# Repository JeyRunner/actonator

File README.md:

## Actonator - 3D Printable Robot Actuator

3D printable robot actuator with belt-driven gearbox and custom FOC driver board for the used BLDC motor.
It uses the [CAN SOT Protocol](https://github.com/JeyRunner/can-sot-protocol) for the communication, which allows to not only send commands and receive state changes but also to set configuration parameters dynamically during runtime.

### Features

- Driver board
  - Input: 10 - 24V
  - Output: can drive up to two BLDC motors, each output up to 10A
  - CAN bus communication
  - Encoders connected via two I2C connections
      - Alternatively via two SPI inputs
    - 12 bit encoders
- Gearbox
  - Fully 3d printable
  - 2 stage timing belt based reduction
  - Simple screw-based belt tensioning mechanism
  - ~1:20 reduction
  - Easily back drivable

### Project Structure
- `motor_driver/firmware`: C++ firmware code for the stm32 microcontroller
- `motor_driver/can_client_lib`: Contains the can bus communication protocol definition and host applications to configure and interface with the motor driver.
    - `motorControllerCanProtocol.def.yaml`: Contains the protocol definition.
- `motor_driver/hardware`: Kicad files with schematics for the board and PCB.
- `motor_driver/hardware/output`: Schematics, board layout and manufacturing files.
- `gearbox`: 3D printing stl files for the gearbox.

### Driver Board Electronics
This board is a dual channel brushless motor driver.
The design of the board can be found in the `hardware` subfolder.
In `hardware/output` are all generated files for all versions.

For the full schematic, see [hardware/motorDriver/output/v0.0.1/schematic.pdf](motor_driver/hardware/output/v0.0.1/schematic.pdf).

### Gearbox

### Usage
First look at [motor_driver/can_client_lib/README.md](motor_driver/can_client_lib/README.md) to compile the communication lib and host control application.
Then compile and flash the microcontroller firmware, see [motor_driver/firmware/README.md](motor_driver/firmware/README.md).

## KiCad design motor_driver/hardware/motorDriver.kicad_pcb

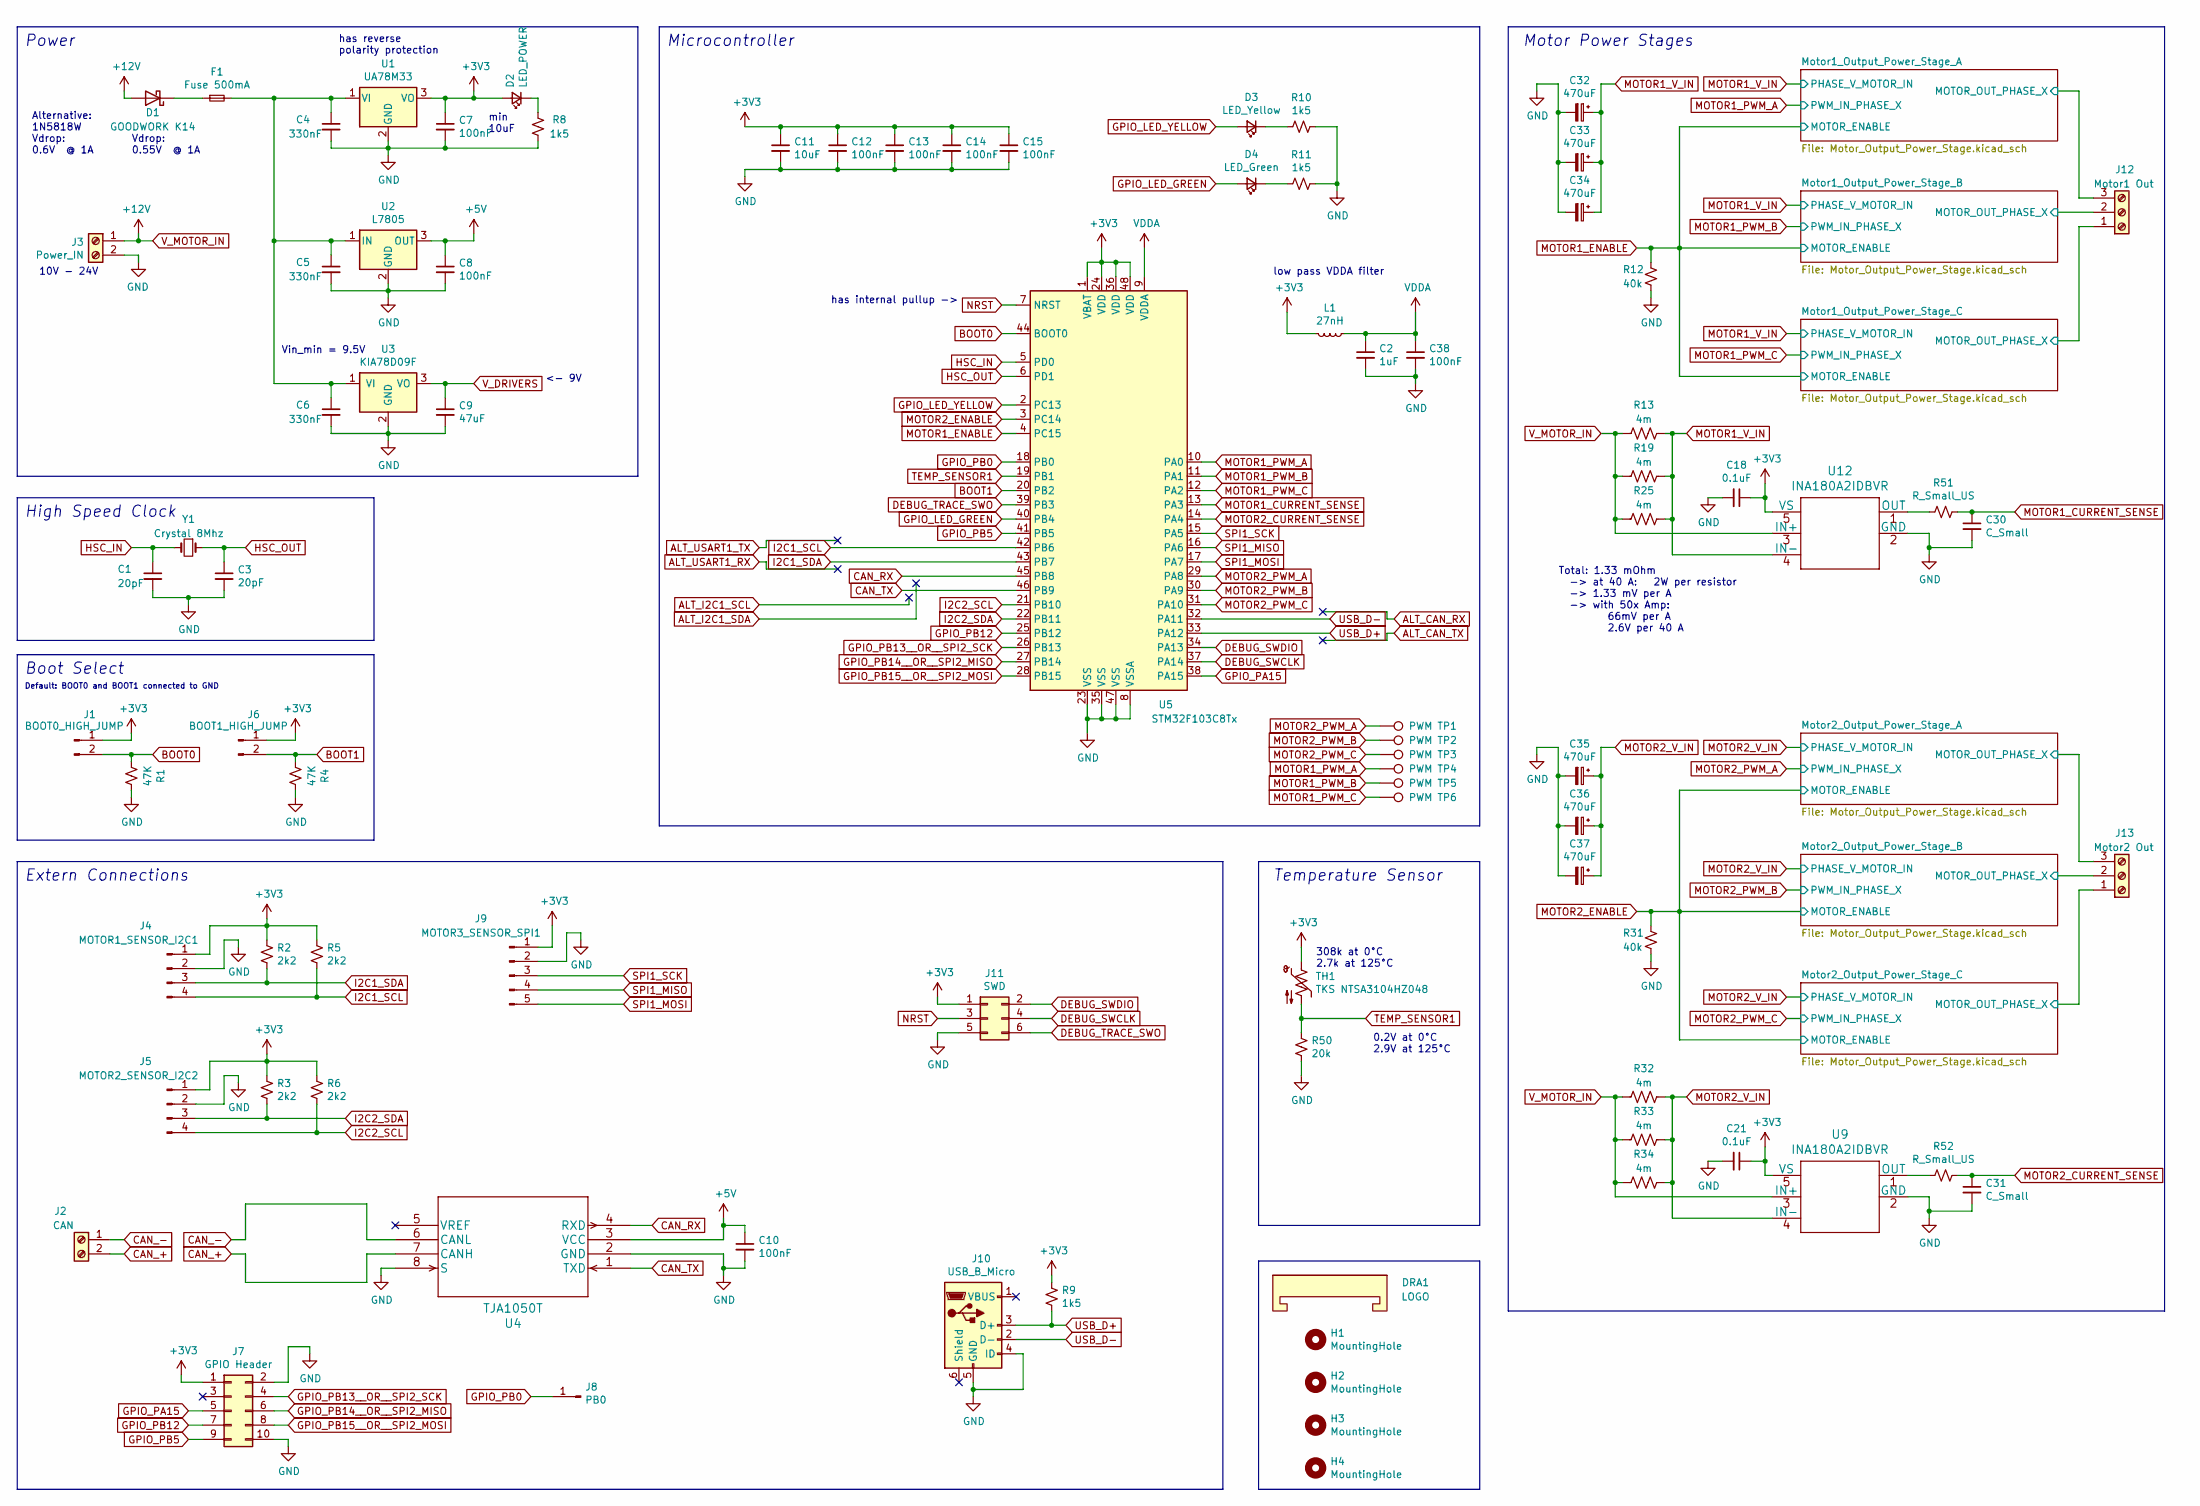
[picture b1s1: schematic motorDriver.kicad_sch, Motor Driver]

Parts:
C1, C3: 20pF; C_0805_2012Metric_Pad1.15x1.40mm_HandSolder
C2: 1uF; C_0805_2012Metric_Pad1.15x1.40mm_HandSolder
C4, C5, C6: 330nF; C_0805_2012Metric_Pad1.15x1.40mm_HandSolder
C7, C8, C10, C12, C13, C14, C15, C38: 100nF; C_0805_2012Metric_Pad1.15x1.40mm_HandSolder
C9: 47uF; C_1210_3225Metric_Pad1.42x2.65mm_HandSolder
C11: 10uF; C_0805_2012Metric_Pad1.15x1.40mm_HandSolder
C18, C21: 0.1uF; C_0805_2012Metric_Pad1.15x1.40mm_HandSolder
C30, C31: C_Small; C_0805_2012Metric_Pad1.15x1.40mm_HandSolder
C32, C33, C34, C35, C36, C37: 470uF; CP_Elec_10x10.5
D1: GOODWORK K14; D_SOD-123F
D2: LED_POWER; LED_0805_2012Metric_Pad1.15x1.40mm_HandSolder
D3: LED_Yellow; LED_0805_2012Metric_Pad1.15x1.40mm_HandSolder
D4: LED_Green; LED_0805_2012Metric_Pad1.15x1.40mm_HandSolder
DRA1: LOGO; logo
F1: Fuse 500mA; Fuse_1206_3216Metric_Pad1.42x1.75mm_HandSolder
H1, H2, H3, H4: MountingHole; MountingHole_3.2mm_M3_DIN965_Pad
J1: BOOT0_HIGH_JUMP; PinHeader_1x02_P1.27mm_Vertical__smallerOutline
J2: CAN; TerminalBlock_RND_205-00045_1x02_P5.00mm_Horizontal
J3: Power_IN; TerminalBlock_RND_205-00045_1x02_P5.00mm_Horizontal___with_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
J4: MOTOR1_SENSOR_I2C1; PinHeader_1x04_P2.54mm_Vertical
J5: MOTOR2_SENSOR_I2C2; PinHeader_1x04_P2.54mm_Vertical
J6: BOOT1_HIGH_JUMP; PinHeader_1x02_P1.27mm_Vertical__smallerOutline
J7: GPIO Header; PinSocket_2x05_P2.54mm_Vertical
J8: PB0; TestPoint_Pad_D1.5mm
J9: MOTOR3_SENSOR_SPI1; PinHeader_1x05_P2.54mm_Vertical
J10: USB_B_Micro; XKB_U254-051T-4BH83-F1S
J11: SWD; PinHeader_2x03_P2.54mm_Vertical
J12: Motor1 Out; TerminalBlock_RND_205-00046_1x03_P5.00mm_Horizontal__extend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
J13: Motor2 Out; TerminalBlock_RND_205-00046_1x03_P5.00mm_Horizontal__extend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
L1: 27nH; L_0603_1608Metric_Pad1.05x0.95mm_HandSolder
R1, R4: 47K; R_1206_3216Metric_Pad1.42x1.75mm_HandSolder
R2, R3, R5, R6: 2k2; R_1206_3216Metric_Pad1.42x1.75mm_HandSolder
R8, R9, R10, R11: 1k5; R_1206_3216Metric_Pad1.42x1.75mm_HandSolder
R12, R31: 40k; R_1206_3216Metric_Pad1.42x1.75mm_HandSolder
R13, R19, R25, R32, R33, R34: 4m; R_2512_6332Metric_Pad1.52x3.35mm_HandSolder
R50: 20k; R_1206_3216Metric_Pad1.42x1.75mm_HandSolder
R51, R52: R_Small_US; R_1206_3216Metric_Pad1.42x1.75mm_HandSolder
TH1: TKS NTSA3104HZ048; TH_2PIN_1.27mm
TP1, TP2, TP3, TP4, TP5, TP6: PWM; TestPoint_Pad_D1.0mm
U1: UA78M33; SOT-223-3_TabPin2
U2: L7805; TO-252-2
U3: KIA78D09F; TO-252-2
U4: TJA1050T
U5: STM32F103C8Tx; LQFP-48_7x7mm_P0.5mm
U9, U12: INA180A2IDBVR; SOT-23-5_HandSoldering
Y1: Crystal 8Mhz; Crystal_HC50_Vertical

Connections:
+3V3: C7.1, C11.1, C12.1, C13.1, C14.1, C15.1, C18.1, C21.1, D2.2 (A), J1.1, J4.1, J5.1, J6.1, J7.1, J9.1, J11.1, L1.2, R2.1, R3.1, R5.1, R6.1, R9.1, TH1.1, U1.3 (VO), U5.1 (VBAT), U5.24 (VDD), U5.36 (VDD), U5.48 (VDD), U9.5 (VS), U12.5 (VS)
+5V: C8.1, C10.1, U2.3 (OUT), U4.3 (VCC)
/Motor1_Output_Power_Stage_A/MOTOR_OUT_PHASE_X: J12.3; also elsewhere on the board
/Motor1_Output_Power_Stage_B/MOTOR_OUT_PHASE_X: J12.2; also elsewhere on the board
/Motor1_Output_Power_Stage_C/MOTOR_OUT_PHASE_X: J12.1; also elsewhere on the board
/Motor2_Output_Power_Stage_A/MOTOR_OUT_PHASE_X: J13.3; also elsewhere on the board
/Motor2_Output_Power_Stage_B/MOTOR_OUT_PHASE_X: J13.2; also elsewhere on the board
/Motor2_Output_Power_Stage_C/MOTOR_OUT_PHASE_X: J13.1; also elsewhere on the board
BOOT0: J1.2, R1.2, U5.44 (BOOT0)
BOOT1: J6.2, R4.2, U5.20 (PB2)
CAN_+: J2.2, U4.7 (CANH)
CAN_-: J2.1, U4.6 (CANL)
CAN_RX: U4.4 (RXD), U5.45 (PB8)
CAN_TX: U4.1 (TXD), U5.46 (PB9)
DEBUG_SWCLK: J11.4, U5.37 (PA14)
DEBUG_SWDIO: J11.2, U5.34 (PA13)
DEBUG_TRACE_SWO: J11.6, U5.39 (PB3)
GND: C1.2, C2.2, C3.2, C4.2, C5.2, C6.2, C7.2, C8.2, C9.2, C10.2, C11.2, C12.2, C13.2, C14.2, C15.2, C18.2, C21.2, C30.2, C31.2, C32.2, C33.2, C34.2, C35.2, C36.2, C37.2, C38.2, J3.2, J4.2, J5.2, J7.2, J7.10, J9.2, J10.4 (ID), J10.5 (GND), J11.5, R1.1, R4.1, R8.1, R10.2, R11.2, R12.2, R31.2, R50.2, U1.2 (GND), U2.2 (GND), U3.2 (GND), U4.2 (GND), U4.8 (S), U5.8 (VSSA), U5.23 (VSS), U5.35 (VSS), U5.47 (VSS), U9.2 (GND), U12.2 (GND); also elsewhere on the board
GPIO_LED_GREEN: D4.2 (A), U5.40 (PB4)
GPIO_LED_YELLOW: D3.2 (A), U5.2 (PC13)
GPIO_PA15: J7.5, U5.38 (PA15)
GPIO_PB0: J8.1, U5.18 (PB0)
GPIO_PB5: J7.9, U5.41 (PB5)
GPIO_PB12: J7.7, U5.25 (PB12)
GPIO_PB13__OR__SPI2_SCK: J7.4, U5.26 (PB13)
GPIO_PB14__OR__SPI2_MISO: J7.6, U5.27 (PB14)
GPIO_PB15__OR__SPI2_MOSI: J7.8, U5.28 (PB15)
HSC_IN: C1.1, U5.5 (PD0), Y1.2
HSC_OUT: C3.1, U5.6 (PD1), Y1.1
I2C1_SCL: J4.4, R5.2, U5.42 (PB6)
I2C1_SDA: J4.3, R2.2, U5.43 (PB7)
I2C2_SCL: J5.4, R6.2, U5.21 (PB10)
I2C2_SDA: J5.3, R3.2, U5.22 (PB11)
MOTOR1_CURRENT_SENSE: C30.1, R51.1, U5.13 (PA3)
MOTOR1_ENABLE: R12.1, U5.4 (PC15); also elsewhere on the board
MOTOR1_PWM_A: TP4.1, U5.10 (PA0); also elsewhere on the board
MOTOR1_PWM_B: TP5.1, U5.11 (PA1); also elsewhere on the board
MOTOR1_PWM_C: TP6.1, U5.12 (PA2); also elsewhere on the board
MOTOR1_V_IN: C32.1, C33.1, C34.1, R13.1, R19.1, R25.1, U12.4 (IN-); also elsewhere on the board
MOTOR2_CURRENT_SENSE: C31.1, R52.1, U5.14 (PA4)
MOTOR2_ENABLE: R31.1, U5.3 (PC14); also elsewhere on the board
MOTOR2_PWM_A: TP1.1, U5.29 (PA8); also elsewhere on the board
MOTOR2_PWM_B: TP2.1, U5.30 (PA9); also elsewhere on the board
MOTOR2_PWM_C: TP3.1, U5.31 (PA10); also elsewhere on the board
MOTOR2_V_IN: C35.1, C36.1, C37.1, R32.1, R33.1, R34.1, U9.4 (IN-); also elsewhere on the board
NRST: J11.3, U5.7 (NRST)
unnamed: C4.1, C5.1, C6.1, F1.2, U1.1 (VI), U2.1 (IN), U3.1 (VI)
unnamed: D1.1 (K), F1.1
unnamed: D2.1 (K), R8.2
unnamed: D3.1 (K), R10.1
unnamed: D4.1 (K), R11.1
unnamed: R51.2, U12.1 (OUT)
unnamed: R52.2, U9.1 (OUT)
SPI1_MISO: J9.4, U5.16 (PA6)
SPI1_MOSI: J9.5, U5.17 (PA7)
SPI1_SCK: J9.3, U5.15 (PA5)
TEMP_SENSOR1: R50.1, TH1.2, U5.19 (PB1)
USB_D+: J10.3 (D+), R9.2, U5.33 (PA12)
USB_D-: J10.2 (D-), U5.32 (PA11)
VDDA: C2.1, C38.1, L1.1, U5.9 (VDDA)
V_DRIVERS: C9.1, U3.3 (VO); also elsewhere on the board
V_MOTOR_IN: D1.2 (A), J3.1, R13.2, R19.2, R25.2, R32.2, R33.2, R34.2, U9.3 (IN+), U12.3 (IN+)

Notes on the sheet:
Vdrop: 0.55V @ 1A
Default: BOOT0 and BOOT1 connected to GND
308k at 0°C 2.7k at 125°C
0.2V at 0°C 2.9V at 125°C
has reverse polarity protection
Vin_min = 9.5V
Extern Connections
Alternative: 1N5818W Vdrop: 0.6V @ 1A
Boot Select
10V - 24V
Temperature Sensor
Power
Microcontroller
Total: 1.33 mOhm -> at 40 A: ~{} 2W per resistor -> 1.33 mV per A -> with 50x Amp: 66mV per A 2.6V per 40 A
min 10uF
High Speed Clock
Motor Power Stages
low pass VDDA filter
<- 9V
has internal pullup ->

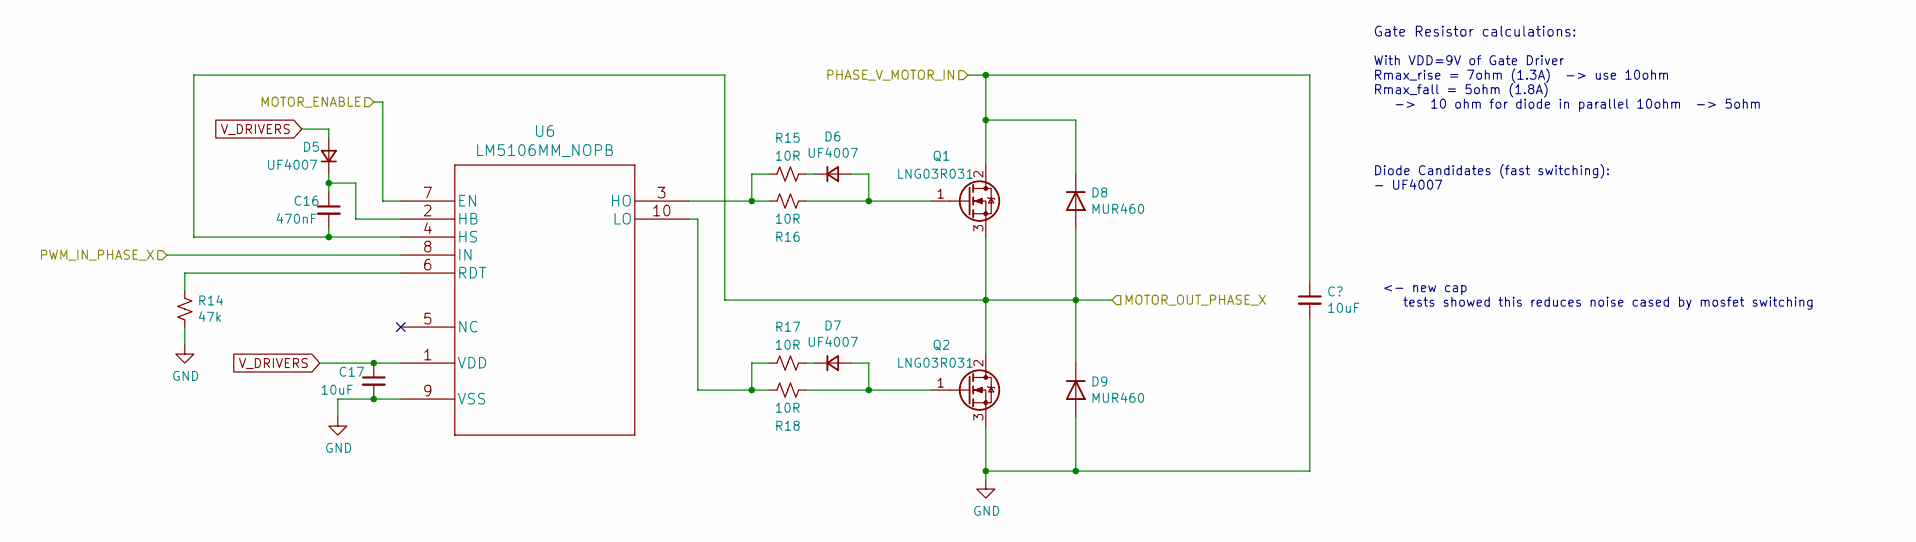
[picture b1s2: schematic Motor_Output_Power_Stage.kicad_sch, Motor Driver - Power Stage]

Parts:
C16: 470nF; C_0805_2012Metric_Pad1.15x1.40mm_HandSolder
C17: 10uF; C_0805_2012Metric_Pad1.15x1.40mm_HandSolder
D5, D6, D7: UF4007; D_T-1_P5.08mm_Horizontal
D8, D9: MUR460; D_DO-15_P10.16mm__H1.4mm_Horizontal
Q1, Q2: LNG03R031; TO-252-2
R14: 47k; R_1206_3216Metric_Pad1.42x1.75mm_HandSolder
R15, R16, R17, R18: 10R; R_1206_3216Metric_Pad1.42x1.75mm_HandSolder
U6: LM5106MM_NOPB; LM5106MM_slash_NOPB

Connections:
/Motor1_Output_Power_Stage_A/MOTOR_OUT_PHASE_X: C16.2, D8.2 (A), D9.1 (K), Q1.3 (S), Q2.2 (D), U6.4 (HS); also elsewhere on the board
GND: C17.2, D9.2 (A), Q2.3 (S), R14.2, U6.9 (VSS); also elsewhere on the board
MOTOR1_ENABLE: U6.7 (EN); also elsewhere on the board
MOTOR1_PWM_A: U6.8 (IN); also elsewhere on the board
MOTOR1_V_IN: D8.1 (K), Q1.2 (D); also elsewhere on the board
unnamed: C16.1, D5.1 (K), U6.2 (HB)
unnamed: D6.1 (K), R15.1
unnamed: D6.2 (A), Q1.1 (G), R16.1
unnamed: D7.1 (K), R17.1
unnamed: D7.2 (A), Q2.1 (G), R18.1
unnamed: R14.1, U6.6 (RDT)
unnamed: R15.2, R16.2, U6.3 (HO)
unnamed: R17.2, R18.2, U6.10 (LO)
V_DRIVERS: C17.1, D5.2 (A), U6.1 (VDD); also elsewhere on the board

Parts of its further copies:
C19, C22, C24, C26, C28: 470nF; C_0805_2012Metric_Pad1.15x1.40mm_HandSolder
C20, C23, C25, C27, C29: 10uF; C_0805_2012Metric_Pad1.15x1.40mm_HandSolder
D10, D11, D12, D15, D16, D17, D20, D21, D22, D25, D26, D27, D30, D31, D32: UF4007; D_T-1_P5.08mm_Horizontal
D13, D14, D18, D19, D23, D24, D28, D29, D33, D34: MUR460; D_DO-15_P10.16mm__H1.4mm_Horizontal
Q3, Q4, Q5, Q6, Q7, Q8, Q9, Q10, Q11, Q12: LNG03R031; TO-252-2
R23, R29, R38, R43, R48: 10R; R_1206_3216Metric_Pad1.42x1.75mm_HandSolder
U7, U8, U10, U11, U13: LM5106MM_NOPB; LM5106MM_slash_NOPB

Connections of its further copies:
/Motor1_Output_Power_Stage_B/MOTOR_OUT_PHASE_X: C19.2, D13.2 (A), D14.1 (K), Q3.3 (S), Q4.2 (D), U7.4 (HS); also elsewhere on the board
/Motor1_Output_Power_Stage_C/MOTOR_OUT_PHASE_X: C22.2, D18.2 (A), D19.1 (K), Q5.3 (S), Q6.2 (D), U8.4 (HS); also elsewhere on the board
/Motor2_Output_Power_Stage_A/MOTOR_OUT_PHASE_X: C24.2, D23.2 (A), D24.1 (K), Q7.3 (S), Q8.2 (D), U10.4 (HS); also elsewhere on the board
/Motor2_Output_Power_Stage_B/MOTOR_OUT_PHASE_X: C26.2, D28.2 (A), D29.1 (K), Q9.3 (S), Q10.2 (D), U11.4 (HS); also elsewhere on the board
/Motor2_Output_Power_Stage_C/MOTOR_OUT_PHASE_X: C28.2, D33.2 (A), D34.1 (K), Q11.3 (S), Q12.2 (D), U13.4 (HS); also elsewhere on the board
GND: C20.2, C23.2, C25.2, C27.2, C29.2, D14.2 (A), D19.2 (A), D24.2 (A), D29.2 (A), D34.2 (A), Q4.3 (S), Q6.3 (S), Q8.3 (S), Q10.3 (S), Q12.3 (S), U7.9 (VSS), U8.9 (VSS), U10.9 (VSS), U11.9 (VSS), U13.9 (VSS); also elsewhere on the board
MOTOR1_ENABLE: U7.7 (EN), U8.7 (EN); also elsewhere on the board
MOTOR1_PWM_B: U7.8 (IN); also elsewhere on the board
MOTOR1_PWM_C: U8.8 (IN); also elsewhere on the board
MOTOR1_V_IN: D13.1 (K), D18.1 (K), Q3.2 (D), Q5.2 (D); also elsewhere on the board
MOTOR2_ENABLE: U10.7 (EN), U11.7 (EN), U13.7 (EN); also elsewhere on the board
MOTOR2_PWM_A: U10.8 (IN); also elsewhere on the board
MOTOR2_PWM_B: U11.8 (IN); also elsewhere on the board
MOTOR2_PWM_C: U13.8 (IN); also elsewhere on the board
MOTOR2_V_IN: D23.1 (K), D28.1 (K), D33.1 (K), Q7.2 (D), Q9.2 (D), Q11.2 (D); also elsewhere on the board
unnamed: C19.1, D10.1 (K), U7.2 (HB)
unnamed: C22.1, D15.1 (K), U8.2 (HB)
unnamed: C24.1, D20.1 (K), U10.2 (HB)
unnamed: C26.1, D25.1 (K), U11.2 (HB)
unnamed: C28.1, D30.1 (K), U13.2 (HB)
unnamed 61: D11.1 (K); also elsewhere on the board
unnamed 62: D11.2 (A), Q3.1 (G); also elsewhere on the board
unnamed: D12.1 (K), R23.1
unnamed 64: D12.2 (A), Q4.1 (G); also elsewhere on the board
unnamed 65: D16.1 (K); also elsewhere on the board
unnamed 66: D16.2 (A), Q5.1 (G); also elsewhere on the board
unnamed: D17.1 (K), R29.1
unnamed 68: D17.2 (A), Q6.1 (G); also elsewhere on the board
unnamed 69: D21.1 (K); also elsewhere on the board
unnamed 70: D21.2 (A), Q7.1 (G); also elsewhere on the board
unnamed: D22.1 (K), R38.1
unnamed 72: D22.2 (A), Q8.1 (G); also elsewhere on the board
unnamed 73: D26.1 (K); also elsewhere on the board
unnamed 74: D26.2 (A), Q9.1 (G); also elsewhere on the board
unnamed: D27.1 (K), R43.1
unnamed 76: D27.2 (A), Q10.1 (G); also elsewhere on the board
unnamed 77: D31.1 (K); also elsewhere on the board
unnamed 78: D31.2 (A), Q11.1 (G); also elsewhere on the board
unnamed: D32.1 (K), R48.1
unnamed 80: D32.2 (A), Q12.1 (G); also elsewhere on the board
unnamed 84: U7.6 (RDT); also elsewhere on the board
unnamed 85: U7.3 (HO); also elsewhere on the board
unnamed 86: R23.2, U7.10 (LO); also elsewhere on the board
unnamed 87: U8.6 (RDT); also elsewhere on the board
unnamed 88: U8.3 (HO); also elsewhere on the board
unnamed 89: R29.2, U8.10 (LO); also elsewhere on the board
unnamed 90: U10.6 (RDT); also elsewhere on the board
unnamed 91: U10.3 (HO); also elsewhere on the board
unnamed 92: R38.2, U10.10 (LO); also elsewhere on the board
unnamed 93: U11.6 (RDT); also elsewhere on the board
unnamed 94: U11.3 (HO); also elsewhere on the board
unnamed 95: R43.2, U11.10 (LO); also elsewhere on the board
unnamed 96: U13.6 (RDT); also elsewhere on the board
unnamed 97: U13.3 (HO); also elsewhere on the board
unnamed 98: R48.2, U13.10 (LO); also elsewhere on the board
V_DRIVERS: C20.1, C23.1, C25.1, C27.1, C29.1, D10.2 (A), D15.2 (A), D20.2 (A), D25.2 (A), D30.2 (A), U7.1 (VDD), U8.1 (VDD), U10.1 (VDD), U11.1 (VDD), U13.1 (VDD); also elsewhere on the board

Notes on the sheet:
<- new cap tests showed this reduces noise cased by mosfet switching
With VDD=9V of Gate Driver Rmax_rise = 7ohm (1.3A) -> use 10ohm Rmax_fall = 5ohm (1.8A) -> 10 ohm for diode in parallel 10ohm -> 5ohm
Diode Candidates (fast switching): - UF4007
Gate Resistor calculations:

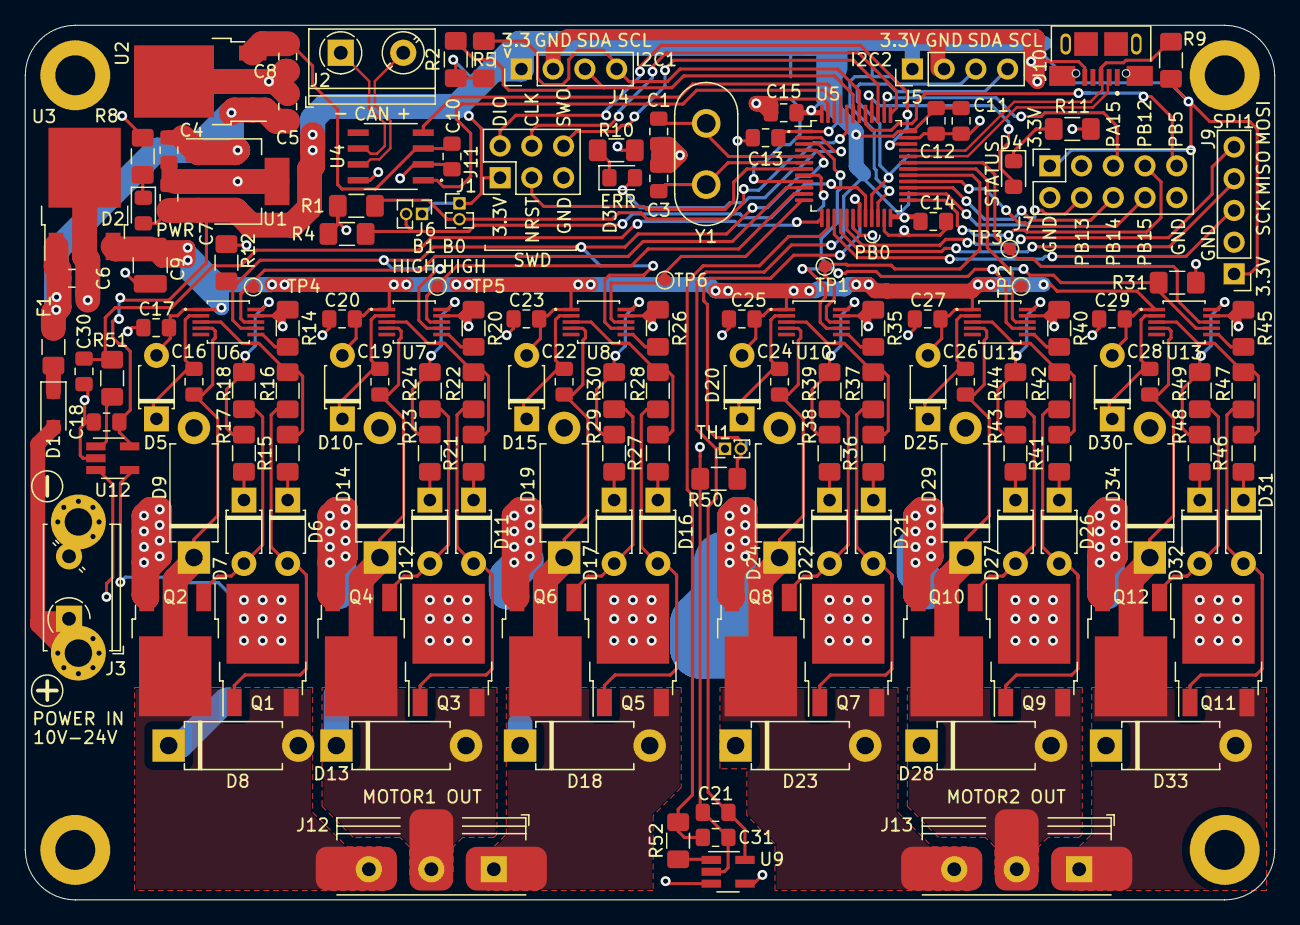
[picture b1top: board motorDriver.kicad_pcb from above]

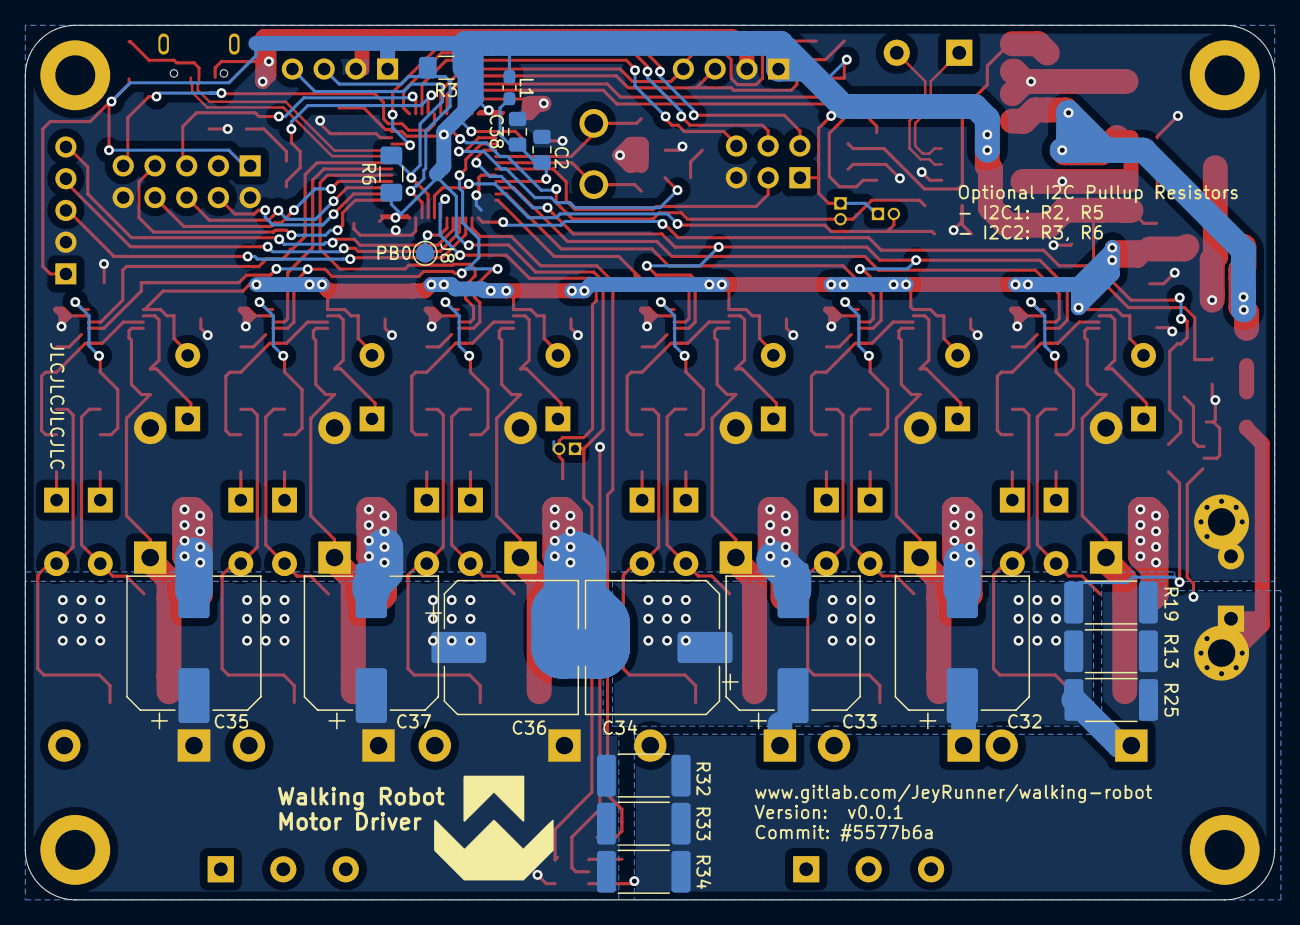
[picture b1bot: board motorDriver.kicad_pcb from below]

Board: 2 copper layers, 100.0 x 70.0 mm, 177 parts (19 on the bottom side), 110 nets.

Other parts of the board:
R20, R26, R35, R40, R45: 47R; R_1206_3216Metric_Pad1.42x1.75mm_HandSolder
R21, R27, R36, R41, R46: 5R; R_1206_3216Metric_Pad1.42x1.75mm_HandSolder
R22, R28, R37, R42, R47: 3.3R; R_1206_3216Metric_Pad1.42x1.75mm_HandSolder
R24, R30, R39, R44, R49: 22R; R_1206_3216Metric_Pad1.42x1.75mm_HandSolder
kibuzzard-642D7167: G***; kibuzzard-642D7167

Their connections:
GND: R20.2, R26.2, R35.2, R40.2, R45.2; also elsewhere on the board
unnamed 61: R21.1; also elsewhere on the board
unnamed 62: R22.1; also elsewhere on the board
unnamed 64: R24.1; also elsewhere on the board
unnamed 65: R27.1; also elsewhere on the board
unnamed 66: R28.1; also elsewhere on the board
unnamed 68: R30.1; also elsewhere on the board
unnamed 69: R36.1; also elsewhere on the board
unnamed 70: R37.1; also elsewhere on the board
unnamed 72: R39.1; also elsewhere on the board
unnamed 73: R41.1; also elsewhere on the board
unnamed 74: R42.1; also elsewhere on the board
unnamed 76: R44.1; also elsewhere on the board
unnamed 77: R46.1; also elsewhere on the board
unnamed 78: R47.1; also elsewhere on the board
unnamed 80: R49.1; also elsewhere on the board
unnamed 84: R20.1; also elsewhere on the board
unnamed 85: R21.2, R22.2; also elsewhere on the board
unnamed 86: R24.2; also elsewhere on the board
unnamed 87: R26.1; also elsewhere on the board
unnamed 88: R27.2, R28.2; also elsewhere on the board
unnamed 89: R30.2; also elsewhere on the board
unnamed 90: R35.1; also elsewhere on the board
unnamed 91: R36.2, R37.2; also elsewhere on the board
unnamed 92: R39.2; also elsewhere on the board
unnamed 93: R40.1; also elsewhere on the board
unnamed 94: R41.2, R42.2; also elsewhere on the board
unnamed 95: R44.2; also elsewhere on the board
unnamed 96: R45.1; also elsewhere on the board
unnamed 97: R46.2, R47.2; also elsewhere on the board
unnamed 98: R49.2; also elsewhere on the board

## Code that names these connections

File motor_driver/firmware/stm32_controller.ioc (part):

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Mcu.Name=STM32F103C(8-B)Tx
Mcu.Package=LQFP48
Mcu.UserName=STM32F103C8Tx
PA0-WKUP.Signal=S_TIM2_CH1_ETR
PA1.Signal=S_TIM2_CH2
PA10.Signal=S_TIM1_CH3
PA13.Mode=Trace_Asynchronous_SW
PA13.Signal=SYS_JTMS-SWDIO
PA14.Mode=Trace_Asynchronous_SW
PA14.Signal=SYS_JTCK-SWCLK
PA2.Signal=S_TIM2_CH3
PA3.GPIOParameters=GPIO_Label
PA3.GPIO_Label=ADC_MOTOR1_CURRENT_SENSE
PA3.Signal=ADCx_IN3
PA4.GPIOParameters=GPIO_Label
PA4.GPIO_Label=ADC_MOTOR2_CURRENT_SENSE
PA4.Signal=ADCx_IN4
PA5.Mode=Full_Duplex_Master
PA5.Signal=SPI1_SCK
PA6.Mode=Full_Duplex_Master
PA6.Signal=SPI1_MISO
PA7.Mode=Full_Duplex_Master
PA7.Signal=SPI1_MOSI
PA8.Signal=S_TIM1_CH1
PA9.Signal=S_TIM1_CH2
PB1.Signal=ADCx_IN9
PB10.GPIOParameters=GPIO_Pu
PB10.GPIO_Pu=GPIO_PULLUP
PB10.Mode=I2C
PB10.Signal=I2C2_SCL
PB11.GPIOParameters=GPIO_Pu
PB11.GPIO_Pu=GPIO_PULLUP
PB11.Mode=I2C
PB11.Signal=I2C2_SDA
PB13.Mode=Full_Duplex_Master
PB13.Signal=SPI2_SCK
PB14.Mode=Full_Duplex_Master
PB14.Signal=SPI2_MISO
PB15.Mode=Full_Duplex_Master
PB15.Signal=SPI2_MOSI
PB3.Mode=Trace_Asynchronous_SW
PB3.Signal=SYS_JTDO-TRACESWO
PB4.GPIOParameters=GPIO_Label
PB4.GPIO_Label=LED_GREEN
PB4.Signal=GPIO_Output
PB6.GPIOParameters=GPIO_Pu
PB6.GPIO_Pu=GPIO_PULLUP
PB6.Mode=I2C
PB6.Signal=I2C1_SCL
PB7.GPIOParameters=GPIO_Pu
PB7.GPIO_Pu=GPIO_PULLUP
PB7.Mode=I2C
PB7.Signal=I2C1_SDA
PB8.Mode=CAN_Activate
PB8.Signal=CAN_RX
PB9.Mode=CAN_Activate
PB9.Signal=CAN_TX
PC13-TAMPER-RTC.GPIOParameters=GPIO_Label
PC13-TAMPER-RTC.GPIO_Label=LED_YELLOW
PC13-TAMPER-RTC.Signal=GPIO_Output
PC14-OSC32_IN.GPIOParameters=GPIO_Label
PC14-OSC32_IN.GPIO_Label=MOTOR2_ENABLE
PC14-OSC32_IN.Signal=GPIO_Output
PC15-OSC32_OUT.GPIOParameters=GPIO_Label
PC15-OSC32_OUT.GPIO_Label=MOTOR1_ENABLE
PC15-OSC32_OUT.Signal=GPIO_Output
PD0-OSC_IN.Mode=HSE-External-Oscillator
PD0-OSC_IN.Signal=RCC_OSC_IN
PD1-OSC_OUT.Mode=HSE-External-Oscillator
PD1-OSC_OUT.Signal=RCC_OSC_OUT
RCC.SYSCLKFreq_VALUE=72000000
RCC.SYSCLKSource=RCC_SYSCLKSOURCE_PLLCLK
board=custom

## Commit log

2025-11-19 motor_driver firmware
2025-11-19 motor_driver hardware
2025-11-19 readme and doc
2025-11-20 fixes
2025-11-20 added video to readme
2025-11-20 fix readme
2025-11-20 added gearbox cad imgs
2025-11-20 readme fixes
2025-11-20 add license
2025-11-20 add can protocol reference to readme
2025-11-20 cleanup kicad libs

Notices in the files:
parts and their libraries:
Copyright 2021 Accelerated Designs. All rights reserved.
